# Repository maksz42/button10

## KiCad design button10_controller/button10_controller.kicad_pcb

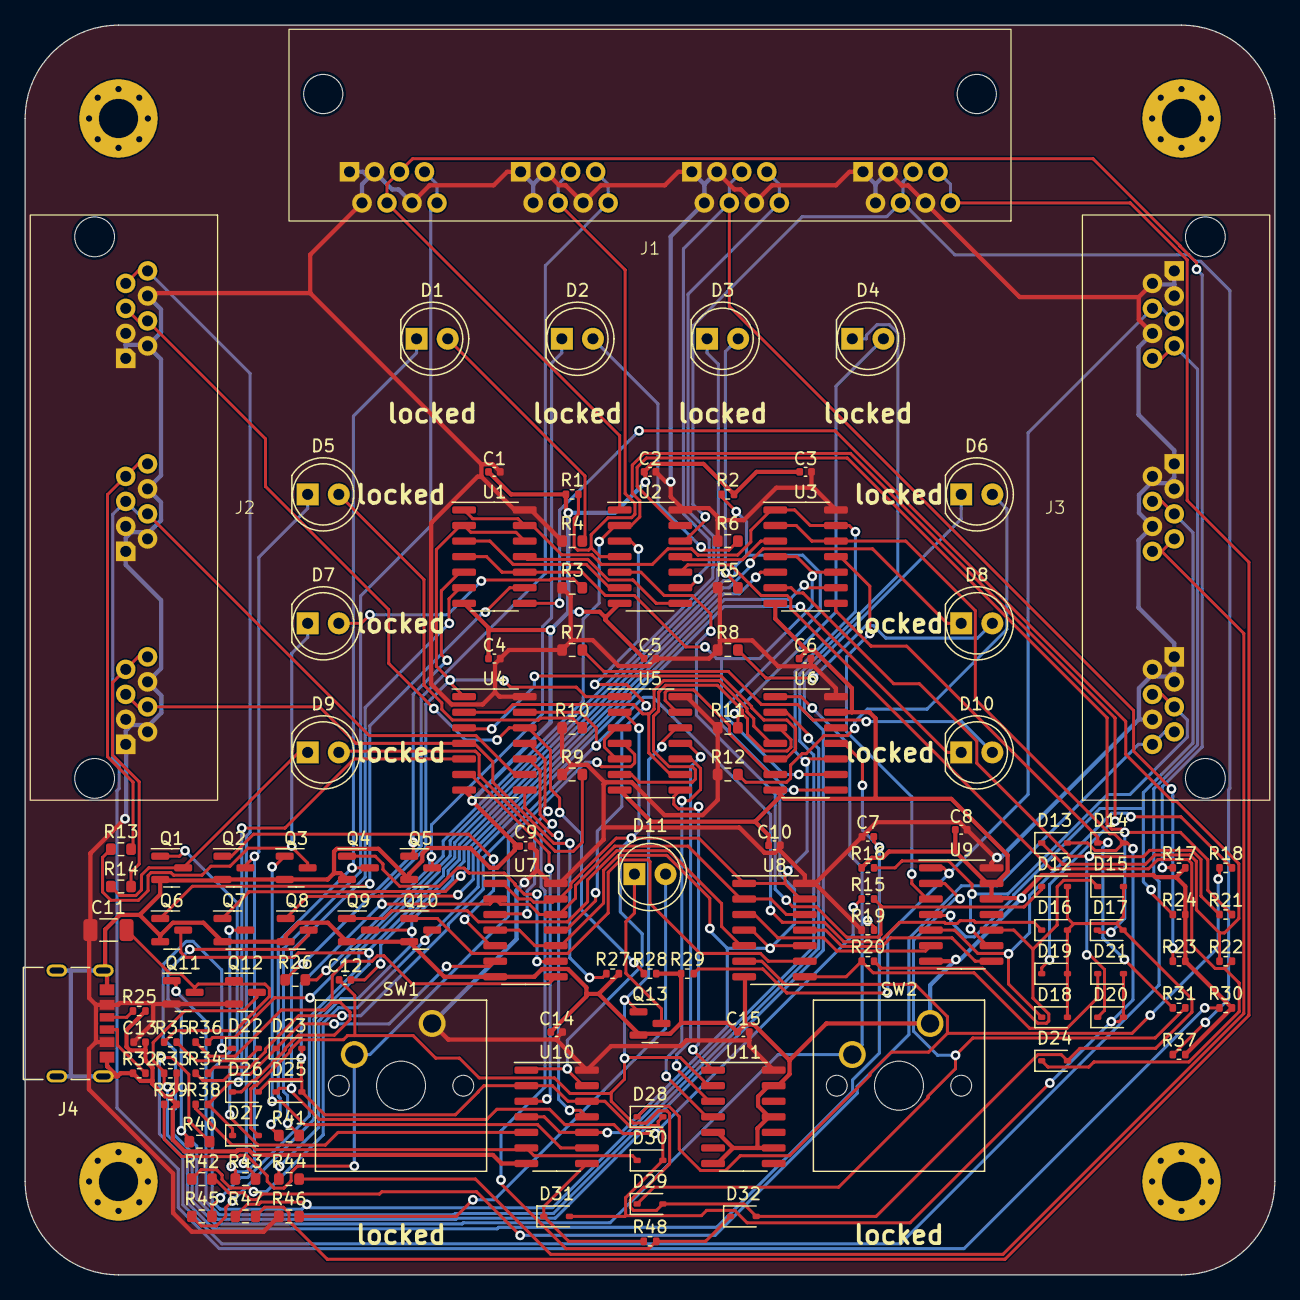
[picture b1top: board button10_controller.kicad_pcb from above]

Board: 2 copper layers, 102.0 x 102.0 mm, 129 parts (0 on the bottom side), 105 nets.

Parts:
C1, C2, C3, C4, C5, C6, C7, C8, C9, C10, C12, C14, C15: 100n; C_0402_1005Metric
C11: 100u; C_1206_3216Metric
C13: 10u; C_0402_1005Metric
D1, D2, D3, D4, D5, D6, D7, D8, D9, D10, D11: LED; LED_D5.0mm
D12, D13, D14, D15, D16, D17, D18, D19, D20, D21, D22, D23, D24, D25, D26, D27, D28, D29, D30, D31, D32: 1N4148WS; D_SOD-323
H1, H2, H3, H4: MountingHole_Pad; MountingHole_3.2mm_M3_Pad_Via
J1: rj45_quad; rj45_quad_RC01406
J2, J3: RJ45_triple; rj45_triple_41207-06G051
J4: USB_C_Receptacle_PowerOnly_6P; USB-TYPE-C-009
Q1, Q2, Q3, Q4, Q5, Q6, Q7, Q8, Q9, Q10, Q13: 2N7002; SOT-23
Q11: BSS84; SOT-23
Q12: S9015; SOT-23
R1, R2, R15, R16, R17, R18, R19, R20, R21, R22, R23, R24, R27, R28, R29, R30, R31, R33, R34, R36, R37, R38, R39, R48: 10k; R_0402_1005Metric
R3, R4, R5, R6, R7, R8, R9, R10, R11, R12, R13, R14, R26, R40, R41, R42, R43, R44, R45, R46, R47: 150; R_0603_1608Metric
R25, R32: 5k1; R_0402_1005Metric
R35: 100k; R_0402_1005Metric
SW1, SW2: SW_Push; SW_Cherry_MX_1.00u_PCB
U1, U3, U7, U8, U10: 74HC74; SOIC-14_3.9x8.7mm_P1.27mm
U2, U4, U5, U9: 74HC08; SOIC-14_3.9x8.7mm_P1.27mm
U6, U11: 74HC14; SOIC-14_3.9x8.7mm_P1.27mm

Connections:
+5V: C1.1, C2.1, C3.1, C4.1, C5.1, C6.1, C7.1, C8.1, C9.1, C10.1, C11.1, C13.1, C14.1, C15.1, J1.1, J1.2, J1.3, J1.6, J1.9, J1.10, J1.11, J1.14, J1.17, J1.18, J1.19, J1.22, J1.25, J1.26, J1.27, J1.30, J2.1, J2.2, J2.3, J2.6, J2.9, J2.10, J2.11, J2.14, J2.17, J2.18, J2.19, J2.22, J3.1, J3.2, J3.3, J3.6, J3.9, J3.10, J3.11, J3.14, J3.17, J3.18, J3.19, J3.22, J4.A9 (VBUS), J4.B9 (VBUS), Q11.2 (S), Q12.2 (E), R3.1, R4.1, R5.1, R6.1, R7.1, R8.1, R9.1, R10.1, R11.1, R12.1, R19.1, R46.1, SW1.1, U1.14 (VCC), U2.14 (VCC), U3.14 (VCC), U4.14 (VCC), U5.14 (VCC), U6.14 (VCC), U7.14 (VCC), U8.14 (VCC), U9.14 (VCC), U10.14 (VCC), U11.14 (VCC)
/data: D13.2 (A), D14.2 (A), D20.2 (A), D21.2 (A), D23.2 (A), D25.2 (A), D26.2 (A), D28.2 (A), D30.2 (A), D31.2 (A), U1.2 (D), U1.12 (D), U3.2 (D), U3.12 (D), U4.1, U5.1, U7.2 (D), U7.12 (D), U8.2 (D), U8.12 (D), U10.2 (D), U10.12 (D)
/flip_flops/set: U1.4 (~S), U1.10 (~S), U3.4 (~S), U3.10 (~S), U6.8, U7.4 (~S), U7.10 (~S), U8.4 (~S), U8.10 (~S), U10.4 (~S), U10.10 (~S)
/flip_flops/sr_flip_flop/R: U5.13, U6.6
/flip_flops/test_mode: C12.1, D12.2 (A), D15.2 (A), D16.2 (A), D17.2 (A), D18.2 (A), D19.2 (A), D24.2 (A), D27.2 (A), D29.2 (A), D32.2 (A), Q13.1 (G), U5.12, U11.2
/reset: U1.1 (~R), U1.13 (~R), U3.1 (~R), U3.13 (~R), U5.2, U6.10, U7.1 (~R), U7.13 (~R), U8.1 (~R), U8.13 (~R), U10.1 (~R), U10.13 (~R)
/test_trig: U4.2, U5.9, U6.4
GND: C1.2, C2.2, C3.2, C4.2, C5.2, C6.2, C8.2, C9.2, C10.2, C13.2, C14.2, C15.2, J4.A12 (GND), J4.B12 (GND), J4.S1 (SHIELD), Q1.2 (S), Q2.2 (S), Q3.2 (S), Q4.2 (S), Q5.2 (S), Q6.2 (S), Q7.2 (S), Q8.2 (S), Q9.2 (S), Q10.2 (S), Q13.2 (S), R1.2, R2.2, R16.2, R17.2, R23.2, R24.2, R25.2, R27.2, R28.2, R29.2, R30.2, R32.2, R33.2, R37.2, R39.2, SW2.1, U1.7 (GND), U2.7 (GND), U3.7 (GND), U4.7 (GND), U5.7 (GND), U6.7 (GND), U6.13, U7.7 (GND), U8.7 (GND), U9.7 (GND), U9.12, U9.13, U10.7 (GND), U11.5, U11.7 (GND), U11.9, U11.11, U11.13
unnamed: C12.2, R2.1, U6.9
unnamed: D1.2 (A), R4.2
unnamed: D1.1 (K), Q4.3 (D), R41.1
unnamed: D2.2 (A), R6.2
unnamed: D2.1 (K), Q5.3 (D), R26.1
unnamed: D3.2 (A), R5.2
unnamed: D3.1 (K), Q6.3 (D), R45.1
unnamed: D4.2 (A), R11.2
unnamed: D4.1 (K), Q7.3 (D), R47.1
unnamed: D5.2 (A), R10.2
unnamed: D5.1 (K), Q2.3 (D), R43.1
unnamed: D6.2 (A), R12.2
unnamed: D6.1 (K), Q8.3 (D), R40.1
unnamed: D7.2 (A), R3.2
unnamed: D7.1 (K), Q3.3 (D), R13.1
unnamed: D8.2 (A), R8.2
unnamed: D8.1 (K), Q9.3 (D), R44.1
unnamed: D9.2 (A), R9.2
unnamed: D9.1 (K), Q1.3 (D), R14.1
unnamed: D10.2 (A), R7.2
unnamed: D10.1 (K), Q10.3 (D), R42.1
unnamed: D11.2 (A), R46.2
unnamed: D11.1 (K), Q13.3 (D)
unnamed: D12.1 (K), R15.2, U2.5
unnamed: D13.1 (K), R22.1, U1.8 (~Q)
unnamed: D14.1 (K), R31.1, U3.8 (~Q)
unnamed: D15.1 (K), R20.2, U9.10
unnamed: D16.1 (K), R34.2, U4.13
unnamed: D17.1 (K), R21.2, U2.13
unnamed: D18.1 (K), R18.2, U9.5
unnamed: D19.1 (K), R36.2, U2.2
unnamed: D20.1 (K), R21.1, U3.6 (~Q)
unnamed: D21.1 (K), R20.1, U8.8 (~Q)
unnamed: D22.2 (A), R35.1
unnamed: D22.1 (K), R19.2, SW2.2, U6.1
unnamed: D23.1 (K), R34.1, U7.6 (~Q)
unnamed: D24.1 (K), R22.2, U2.10
unnamed: D25.1 (K), R15.1, U1.6 (~Q)
unnamed: D26.1 (K), R36.1, U7.8 (~Q)
unnamed: D27.1 (K), R38.2, U4.5
unnamed: D28.1 (K), R18.1, U8.6 (~Q)
unnamed: D29.1 (K), R31.2, U9.2
unnamed: D30.1 (K), R38.1, U10.6 (~Q)
unnamed: D31.1 (K), R48.1, U10.8 (~Q)
unnamed: D32.1 (K), R48.2, U4.10
unnamed: J1.4, J1.5, R17.1, U2.1
unnamed: J1.7, J1.8, R41.2
unnamed: J1.12, J1.13, R1.1, U2.4
unnamed: J1.15, J1.16, R26.2
unnamed: J1.20, J1.21, R23.1, U2.9
unnamed: J1.23, J1.24, R45.2
unnamed: J1.28, J1.29, R37.1, U2.12
unnamed: J1.31, J1.32, R47.2
unnamed: J2.4, J2.5, R27.1, U4.4
unnamed: J2.7, J2.8, R14.2
unnamed: J2.12, J2.13, R30.1, U4.9
unnamed: J2.15, J2.16, R13.2
unnamed: J2.20, J2.21, R28.1, U4.12
unnamed: J2.23, J2.24, R43.2
unnamed: J3.4, J3.5, R29.1, U9.1
unnamed: J3.7, J3.8, R40.2
unnamed: J3.12, J3.13, R24.1, U9.4
unnamed: J3.15, J3.16, R44.2
unnamed: J3.20, J3.21, R16.1, U9.9
unnamed: J3.23, J3.24, R42.2
unnamed: J4.A5 (CC1), R25.1
unnamed: J4.B5 (CC2), R32.1
unnamed: Q1.1 (G), U10.5 (Q)
unnamed: Q2.1 (G), U7.5 (Q)
unnamed: Q3.1 (G), U10.9 (Q)
unnamed: Q4.1 (G), U7.9 (Q)
unnamed: Q5.1 (G), U1.5 (Q)
unnamed: Q6.1 (G), U1.9 (Q)
unnamed: Q7.1 (G), U3.5 (Q)
unnamed: Q8.1 (G), U3.9 (Q)
unnamed: Q9.1 (G), U8.5 (Q)
unnamed: Q10.1 (G), U8.9 (Q)
unnamed: C11.2, Q11.3 (D), Q12.1 (B), R35.2
unnamed: Q11.1 (G), U6.2
unnamed: C7.2, Q12.3 (C), R33.1, U6.11
unnamed: R39.1, SW1.2, U5.4
unnamed: U1.3 (C), U2.6
unnamed: U1.11 (C), U2.8
unnamed: U2.11, U3.3 (C)
unnamed: U3.11 (C), U9.3
unnamed: U4.3, U6.5
unnamed: U5.3, U5.5
unnamed: U5.6, U6.3
unnamed: U4.11, U7.3 (C)
unnamed: U2.3, U7.11 (C)
unnamed: U8.3 (C), U9.6
unnamed: U8.11 (C), U9.8
unnamed: U4.6, U10.3 (C)
unnamed: U4.8, U10.11 (C)
unnamed: U5.8, U11.1
unnamed: U5.11, U11.3
unnamed: U5.10, U11.4

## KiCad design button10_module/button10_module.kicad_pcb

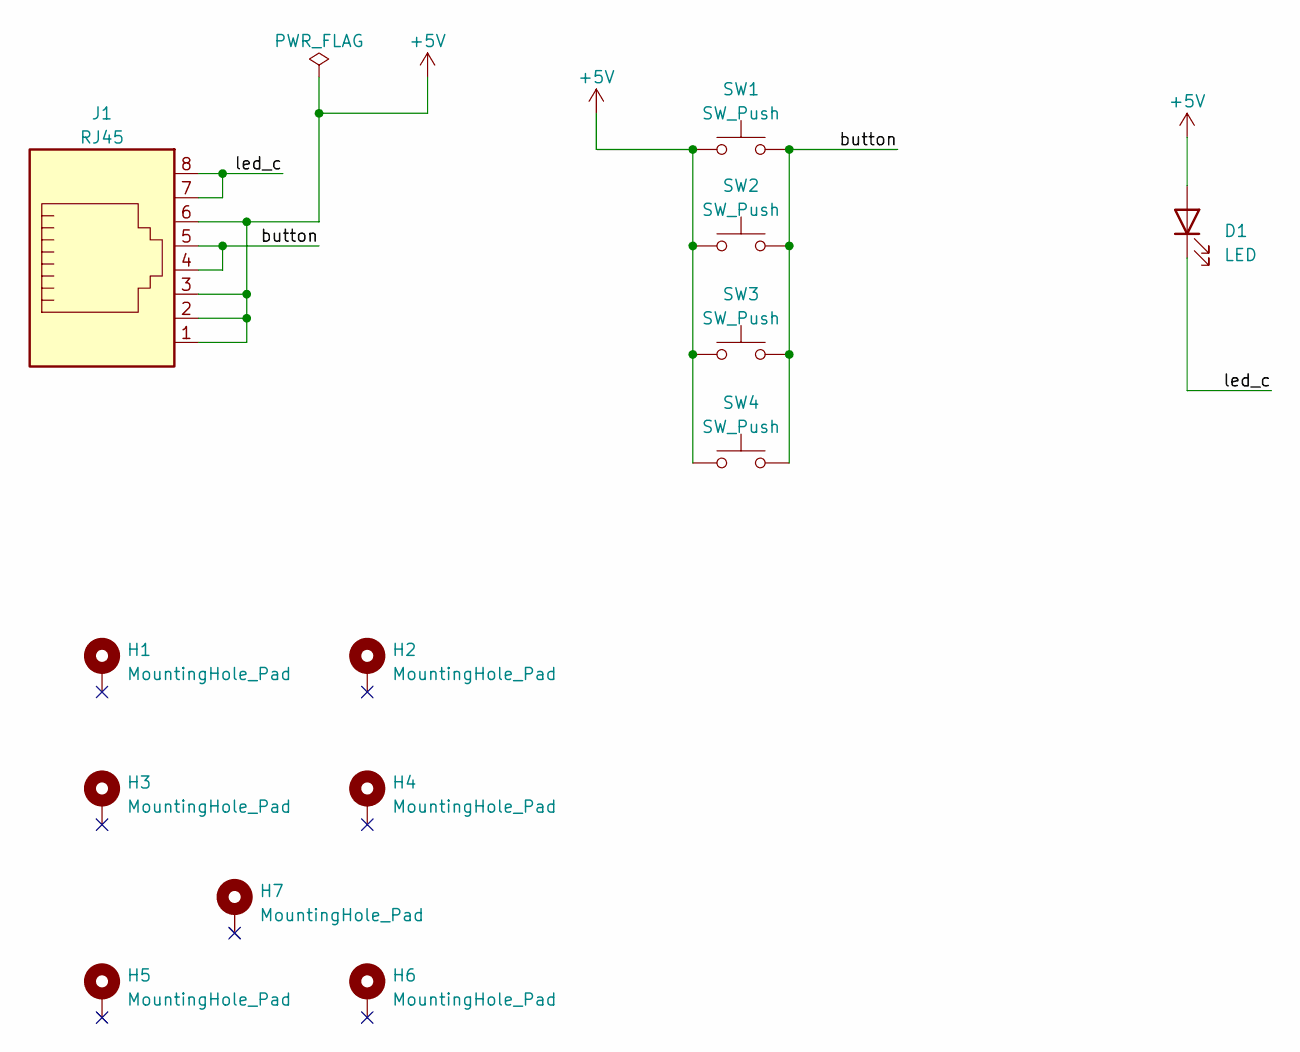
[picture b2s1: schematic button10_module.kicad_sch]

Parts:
D1: LED; LED_D5.0mm
H1, H2, H3, H4, H5, H6, H7: MountingHole_Pad; MountingHole_3.2mm_M3_Pad_Via
J1: RJ45; rj45_single_RC01374; mpn C708627
SW1, SW2, SW3, SW4: SW_Push; SW_Cherry_MX_1.00u_PCB

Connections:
+5V: D1.2 (A), J1.1, J1.2, J1.3, J1.6, SW1.1, SW2.1, SW3.1, SW4.1
/button: J1.4, J1.5, SW1.2, SW2.2, SW3.2, SW4.2
/led_c: D1.1 (K), J1.7, J1.8

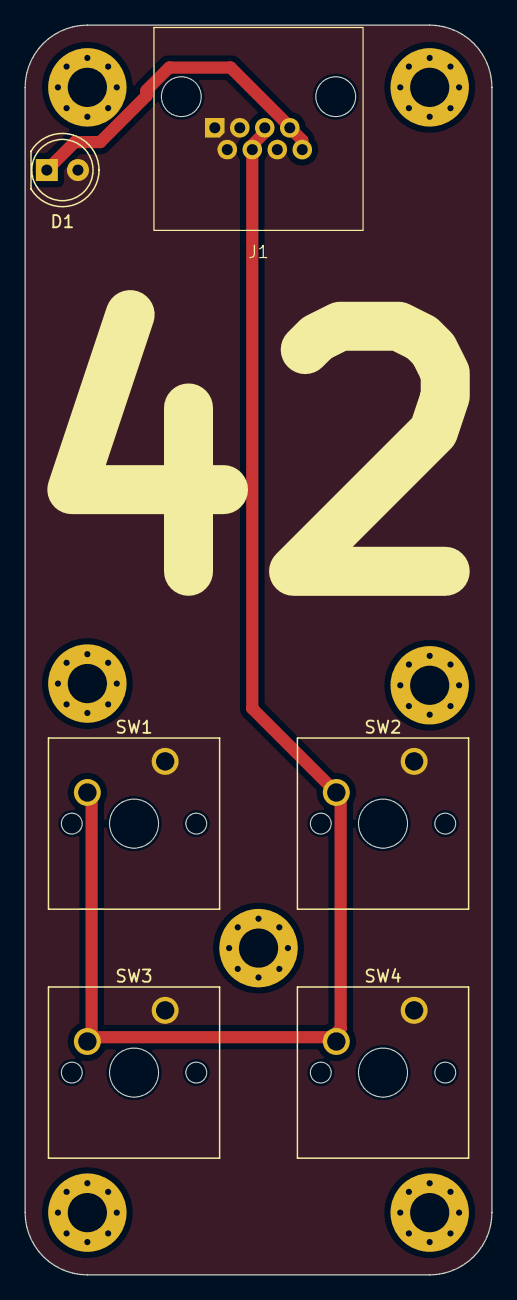
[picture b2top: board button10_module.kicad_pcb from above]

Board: 2 copper layers, 38.1 x 102.0 mm, 13 parts (0 on the bottom side), 3 nets.

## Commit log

2023-07-06 init
